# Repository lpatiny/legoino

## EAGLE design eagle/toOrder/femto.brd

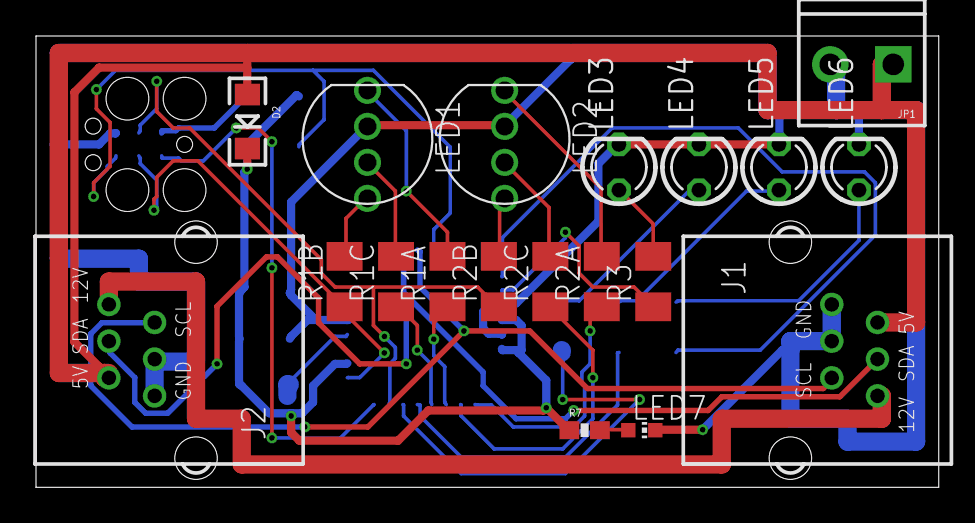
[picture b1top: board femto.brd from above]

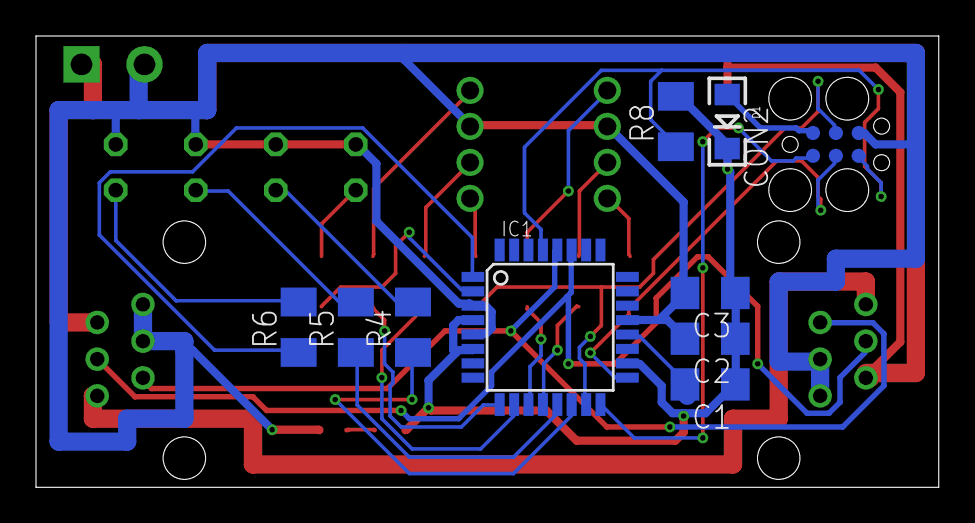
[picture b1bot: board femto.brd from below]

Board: 2 copper layers, 50.2 x 25.1 mm, 29 parts (10 on the bottom side), 31 nets.

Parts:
C1, C2: 0.1uF; C1206
C3: 10uF; C1206
CON2: TC2030-MCP
D1, D2: 1N581D1206; LED-1206
IC1: MEGA8-AI; TQFP32-08
J1, J2: RJ12RIGHTANGLE-I2C; RJ12-RIGHTANGLE-I2C
JP1: SCREWTERMINAL-3.5MM-2
LED1, LED2: RGB-COMMON-CATHODE; LED-TRICOLOR-THROUGHHOLE
LED3, LED4, LED5, LED6: LED3MM
LED7: CHIP-LED0603
R1A, R1B, R1C, R2A, R2B, R2C, R3, R4, R5, R6: 1k; M1206
R7: 10k; 0603-RES
R8: 10k; M1206

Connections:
5V_A: CON2.5V, D1.A
5V_B: D2.A, J1.+5V, J2.+5V, JP1.1
+5V: C1.1, C2.1, C3.1, D1.C, D2.C, IC1.4, IC1.6, IC1.18, R7.1, R8.2
B0: IC1.12, R1C.1
D3: IC1.1, R6.1
D4: IC1.2, R3.1
D5: IC1.9, R2A.1
D6: IC1.10, R2C.1
D7: IC1.11, R1A.1
D9: IC1.13, R5.1
D10: IC1.14, R4.1
GND: C2.2, C3.2, CON2.GND, IC1.3, IC1.5, IC1.21, J1.GND1, J1.GND2, J2.GND1, J2.GND2, JP1.2, LED1.GND, LED2.GND, LED3.K, LED4.K, LED5.K, LED6.K, LED7.C
MISO: CON2.MISO, IC1.16
MOSI: CON2.MOSI, IC1.15, R2B.1
unnamed: LED2.RED, R2A.2
unnamed: C1.2, IC1.20
unnamed: LED2.BLU, R2B.2
unnamed: LED2.GRN, R2C.2
unnamed: J1.+12V, J2.+12V
unnamed: LED7.A, R7.2
unnamed: LED3.A, R3.2
unnamed: LED1.RED, R1A.2
unnamed: LED1.BLU, R1B.2
unnamed: LED1.GRN, R1C.2
unnamed: LED6.A, R6.2
unnamed: LED5.A, R5.2
unnamed: LED4.A, R4.2
RESET: CON2.RESET, IC1.29, R8.1
SCK: CON2.SCK, IC1.17, R1B.1
SCL: IC1.28, J1.SCL, J2.SCL
SDA: IC1.27, J1.SDA, J2.SDA

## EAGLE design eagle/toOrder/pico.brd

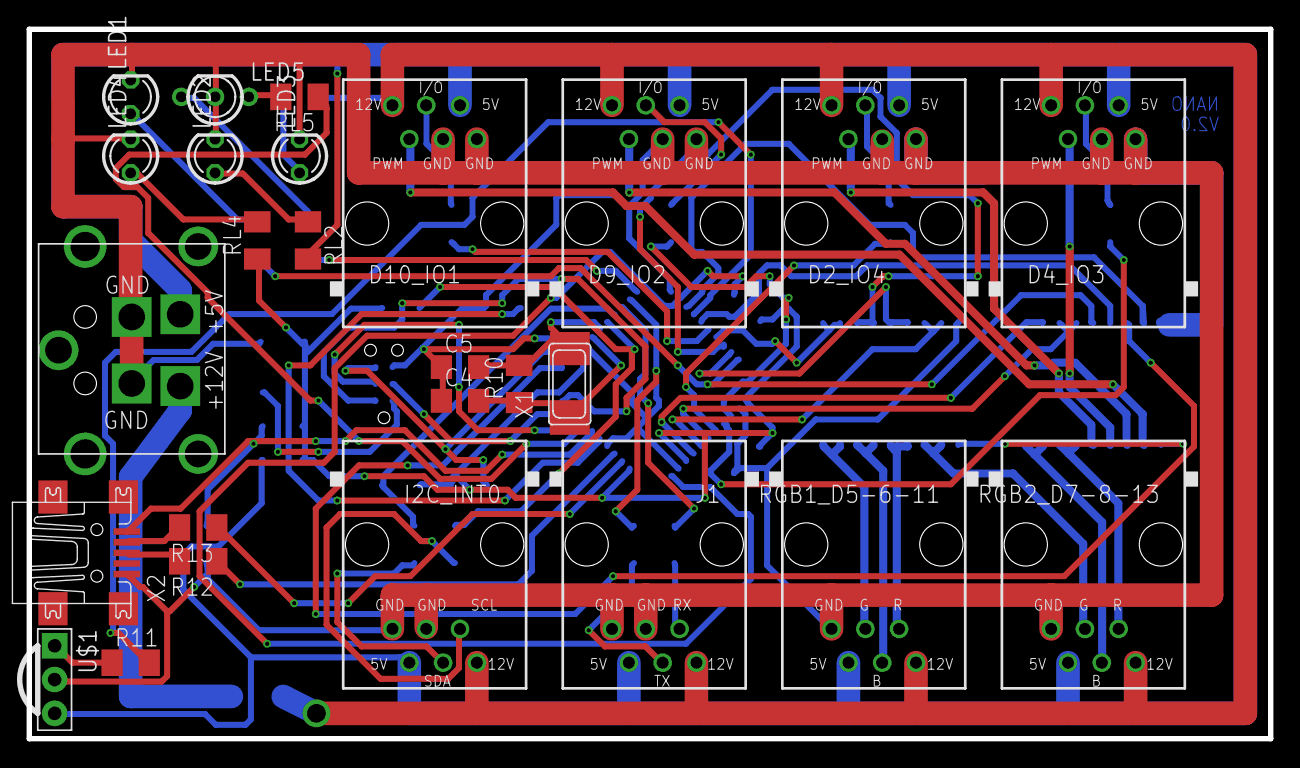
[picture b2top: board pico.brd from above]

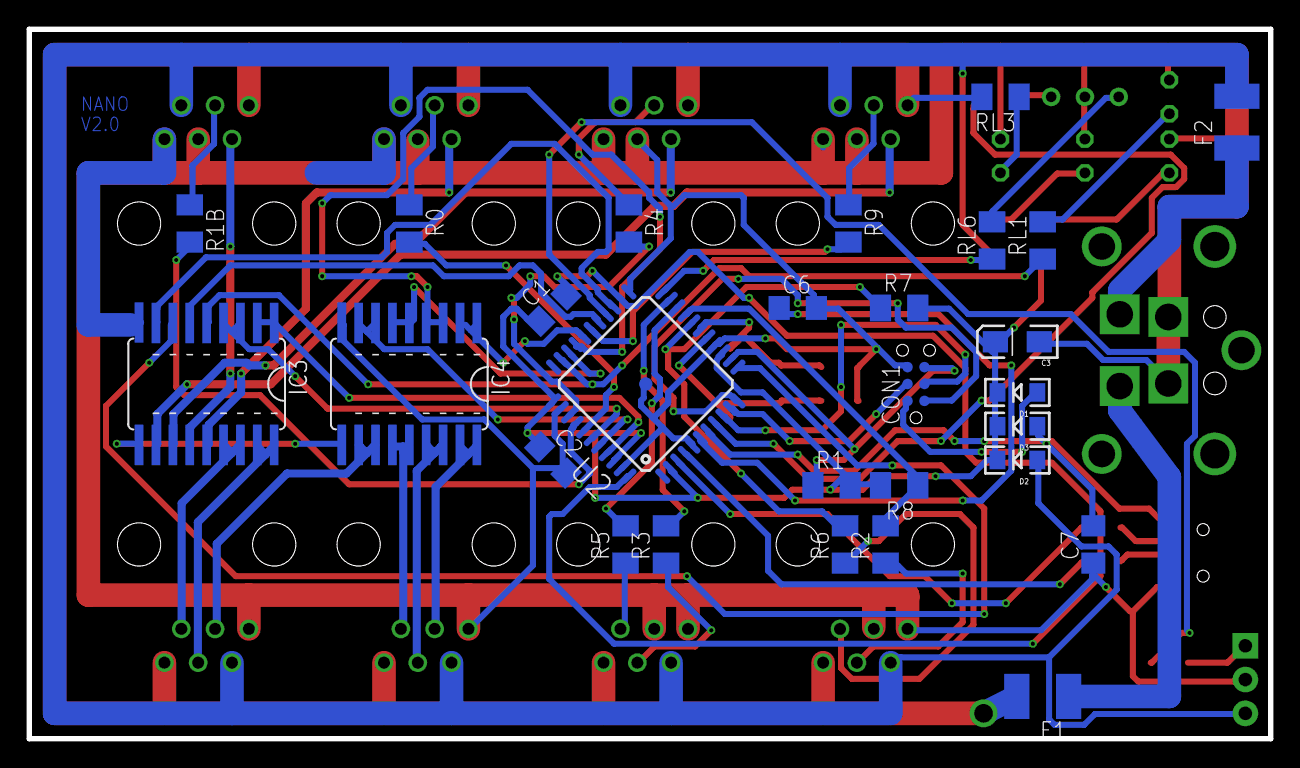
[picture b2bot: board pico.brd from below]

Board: 2 copper layers, 93.3 x 53.3 mm, 54 parts (28 on the bottom side), 67 nets.

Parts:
C1, C2: 0.1uF; C1206
C3: 10uF 20V; EIA3216-KIT
C4, C5: 22pF; C1206
C6: 1uF; C1206
C7: 10uF; C1206
CON1: TC2030-MCP-NL
D1, D2, D3: 1N581D1206; LED-1206
D2_IO4: IO4; RJ12-STRAIGHT
D4_IO3: IO3; RJ12-STRAIGHT
D9_IO2: IO2; RJ12-STRAIGHT
D10_IO1: IO1; RJ12-STRAIGHT
F1, F2: 0.5A; C1812
I2C_INT0: I2C; RJ12-STRAIGHT-I2C
IC3, IC4: ULN2803A; SO18W
J1: RS232; RJ12-STRAIGHT-RS232
LED1: LED3MM
LED2: 5V; LED3MM
LED3: 12V; LED3MM
LED4: 5V uC; LED3MM
LED5: BICOLOR-LED; BICOLOR-3MM
R0, R1B, R2, R3, R4, R5, R6, R9, R11: 1K; M1206
R1: 10k; M1206
R7, R8: 10K; M1206
R10: 1M; M1206
R12, R13: 22; M1206
RGB1_D5-6-11: RGB1; RJ12-STRAIGHT-RGB
RGB2_D7-8-13: RGB2; RJ12-STRAIGHT-RGB
RL1, RL2, RL3, RL4, RL5, RL6: 1K; M1206
U2: ATMEGA32U4-XUAU; TQFP44-PAD
U$1: PNA460XM
U$2: KPJX-4S-S
X1: 16MHz; NX6035
X2: MINI-USB-UX60-MB-5ST; UX60-MB-5ST

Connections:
5V: C1.1, C2.1, C3.A, D1.C, D2.C, D3.C, R1.2, R7.2, R8.2, RL4.1, U2.2, U2.14, U2.34, U2.42
+5V: D2.A, D2_IO4.+5V, D4_IO3.+5V, D9_IO2.+5V, D10_IO1.+5V, F2.2, I2C_INT0.+5V, J1.+5V, RGB1_D5-6-11.+5V, RGB2_D7-8-13.+5V, RL2.2, U$1.3
+12V: D2_IO4.+12V, D4_IO3.+12V, D9_IO2.+12V, D10_IO1.+12V, F1.2, I2C_INT0.+12V, J1.+12V, RGB1_D5-6-11.+12V, RGB2_D7-8-13.+12V, RL3.2
COM: IC3.10, IC4.10
D2B: D9_IO2.I/O, R4.1
D2B1: D10_IO1.I/O, R9.1
D2B4: I2C_INT0.SDA, R2.1
D2B5: J1.TX, R3.1
D2B6: D2_IO4.I/O, R0.1
D2B7: D4_IO3.I/O, R1B.1
D4: IC3.8, U2.25
D5: IC4.5, IC4.6, U2.31
D6: IC3.6, U2.27
D8: R9.2, U2.28
D9: IC4.1, IC4.2, U2.29
D10: IC4.3, IC4.4, U2.30
D11: IC3.7, U2.12
D12: R11.2, U2.26
D13: IC3.5, RL1.1, U2.32
D14: C4.2, R10.1, U2.16, X1.P$2
D15: C5.2, R10.2, U2.17, X1.P$1
D18: R4.2, U2.36
D19: R1B.2, U2.37
D20: R0.2, U2.38
D21: IC3.3, IC3.4, U2.39
D22: IC4.7, IC4.8, U2.40
D23: IC3.1, IC3.2, U2.41
D+: R12.2, X2.3
D-: R13.2, X2.2
GND: C2.2, C3.C, C4.1, C5.1, C6.2, C7.1, CON1.GND, D2_IO4.GND1, D2_IO4.GND2, D4_IO3.GND1, D4_IO3.GND2, D9_IO2.GND1, D9_IO2.GND2, D10_IO1.GND1, D10_IO1.GND2, I2C_INT0.GND1, I2C_INT0.GND2, IC3.9, IC4.9, J1.GND1, J1.GND2, LED1.K, LED2.K, LED3.K, LED4.K, LED5.2, RGB1_D5-6-11.GND1, RGB2_D7-8-13.GND1, U2.5, U2.15, U2.23, U2.35, U2.43, U2.P$1, U$1.2, U$2.GND1, U$2.GND2, X2.5
ISP+5V: CON1.5V, D1.A
MISO: CON1.MISO, U2.11
MOSI: CON1.MOSI, U2.10
unnamed: IC4.17, IC4.18, RGB1_D5-6-11.G
unnamed: D4_IO3.PWM, IC3.13
unnamed: LED1.A, RL1.2
unnamed: C6.1, U2.6
unnamed: F2.1, U$2.+5V
unnamed: LED4.A, RL4.2
unnamed: F1.1, U$2.+12V
unnamed: R11.1, U$1.1
unnamed: C1.2, U2.24, U2.44
unnamed: LED5.3, RL5.2
unnamed: LED5.1, RL6.2
unnamed: IC3.15, IC3.16, RGB2_D7-8-13.R
unnamed: D9_IO2.PWM, IC3.12
unnamed: IC3.17, IC3.18, RGB2_D7-8-13.B
unnamed: IC4.15, IC4.16, RGB1_D5-6-11.B
unnamed: D10_IO1.PWM, IC3.11
unnamed: IC4.11, IC4.12, RGB2_D7-8-13.G
unnamed: D2_IO4.PWM, IC3.14
unnamed: IC4.13, IC4.14, RGB1_D5-6-11.R
unnamed: J1.RX, R5.1
unnamed: I2C_INT0.SCL, R6.1
unnamed: LED3.A, RL3.1
unnamed: LED2.A, RL2.1
RD+: R12.1, U2.4
RD-: R13.1, U2.3
RESET: CON1.RESET, R1.1, U2.13
RX: R5.2, U2.20
RXLED: RL5.1, U2.8
SCK: CON1.SCK, U2.9
SCL: R6.2, R7.1, U2.18
SDA: R2.2, R8.1, U2.19
TX: R3.2, U2.21
TXLED: RL6.1, U2.22
VUSB: C7.2, D3.A, U2.7, X2.1

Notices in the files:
parts and their libraries:
lpatiny: ©2009 ROFA.cz - modified and updated by Robert Darlington ‹rdarlington@gmail.com›
SparkFun: Licensing: CC v3.0 Share-Alike You are welcome to use this library for commercial purposes.
